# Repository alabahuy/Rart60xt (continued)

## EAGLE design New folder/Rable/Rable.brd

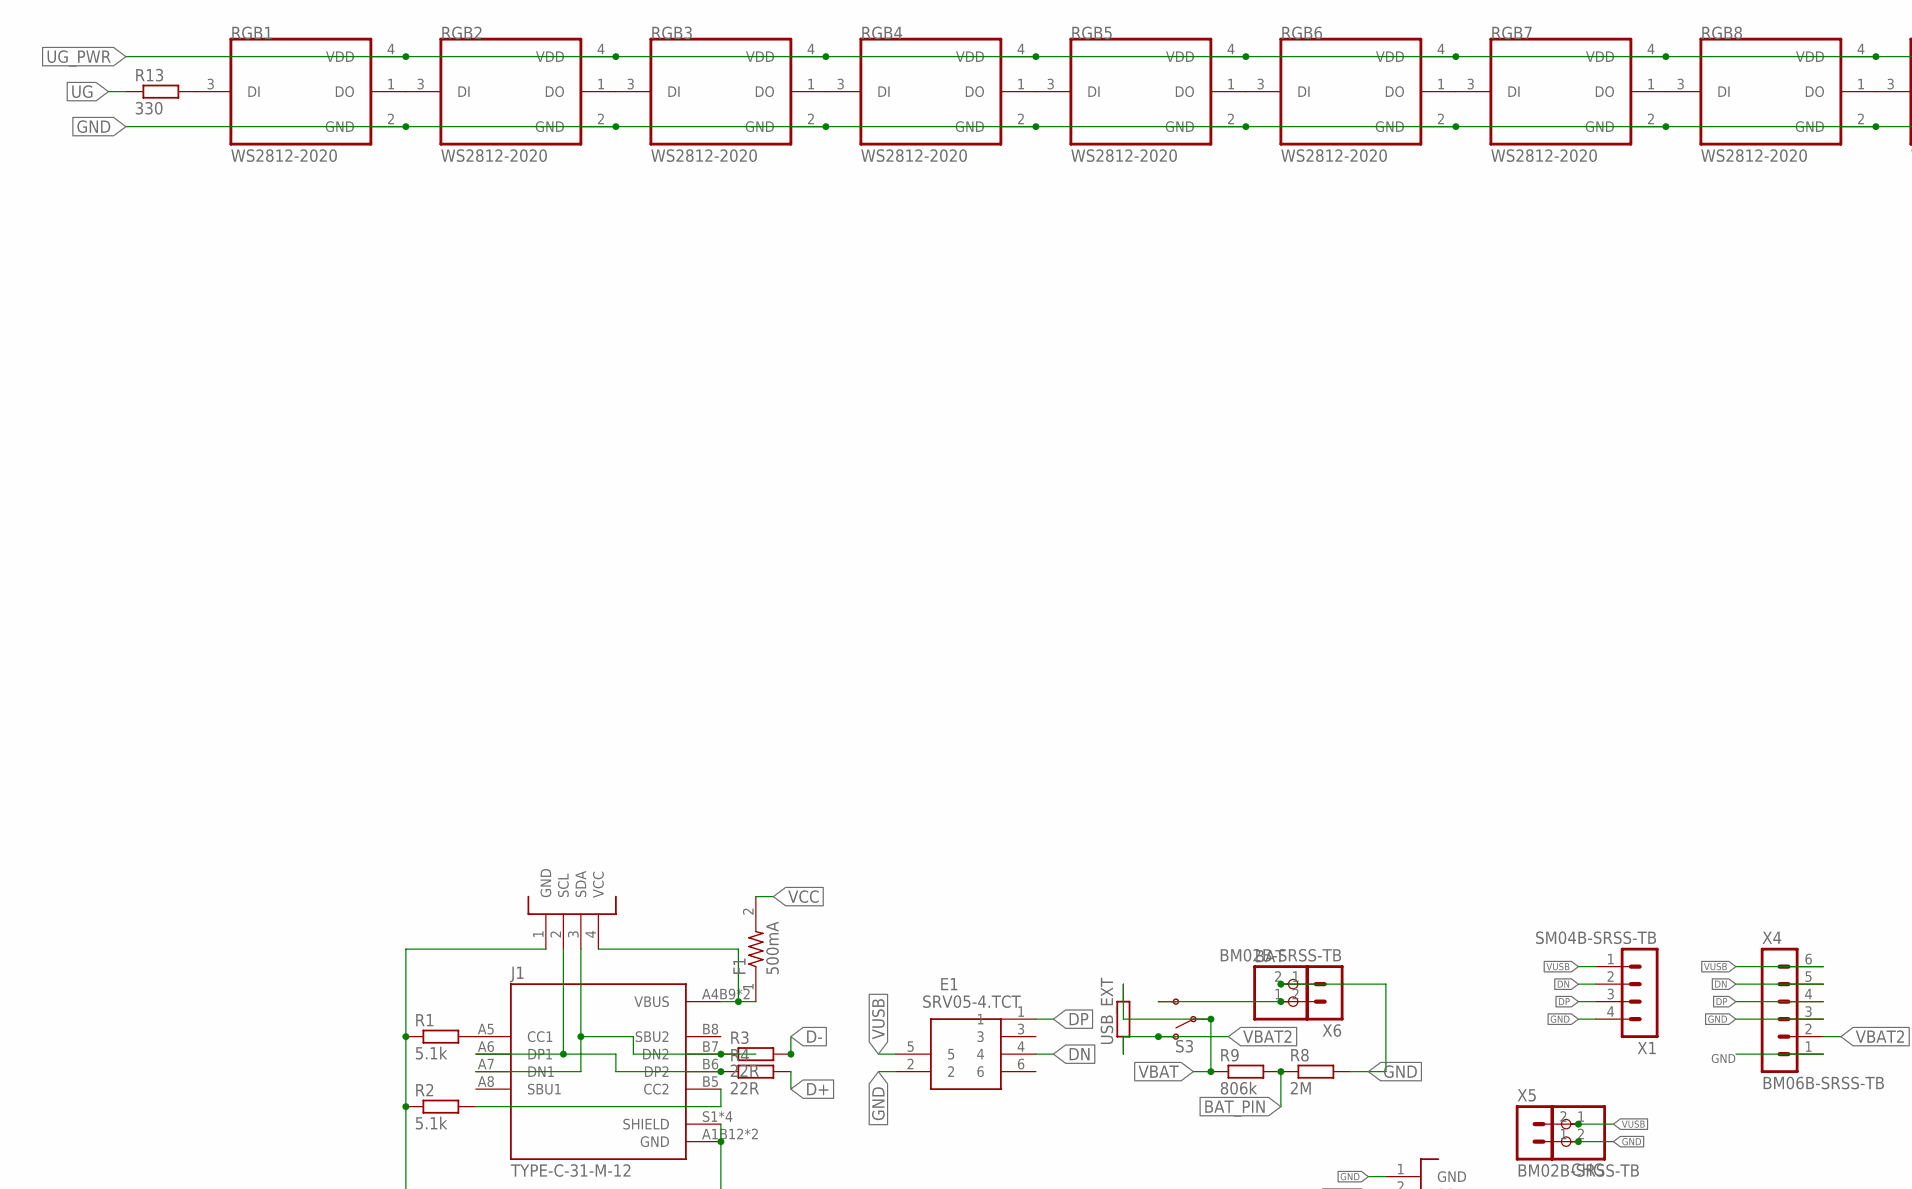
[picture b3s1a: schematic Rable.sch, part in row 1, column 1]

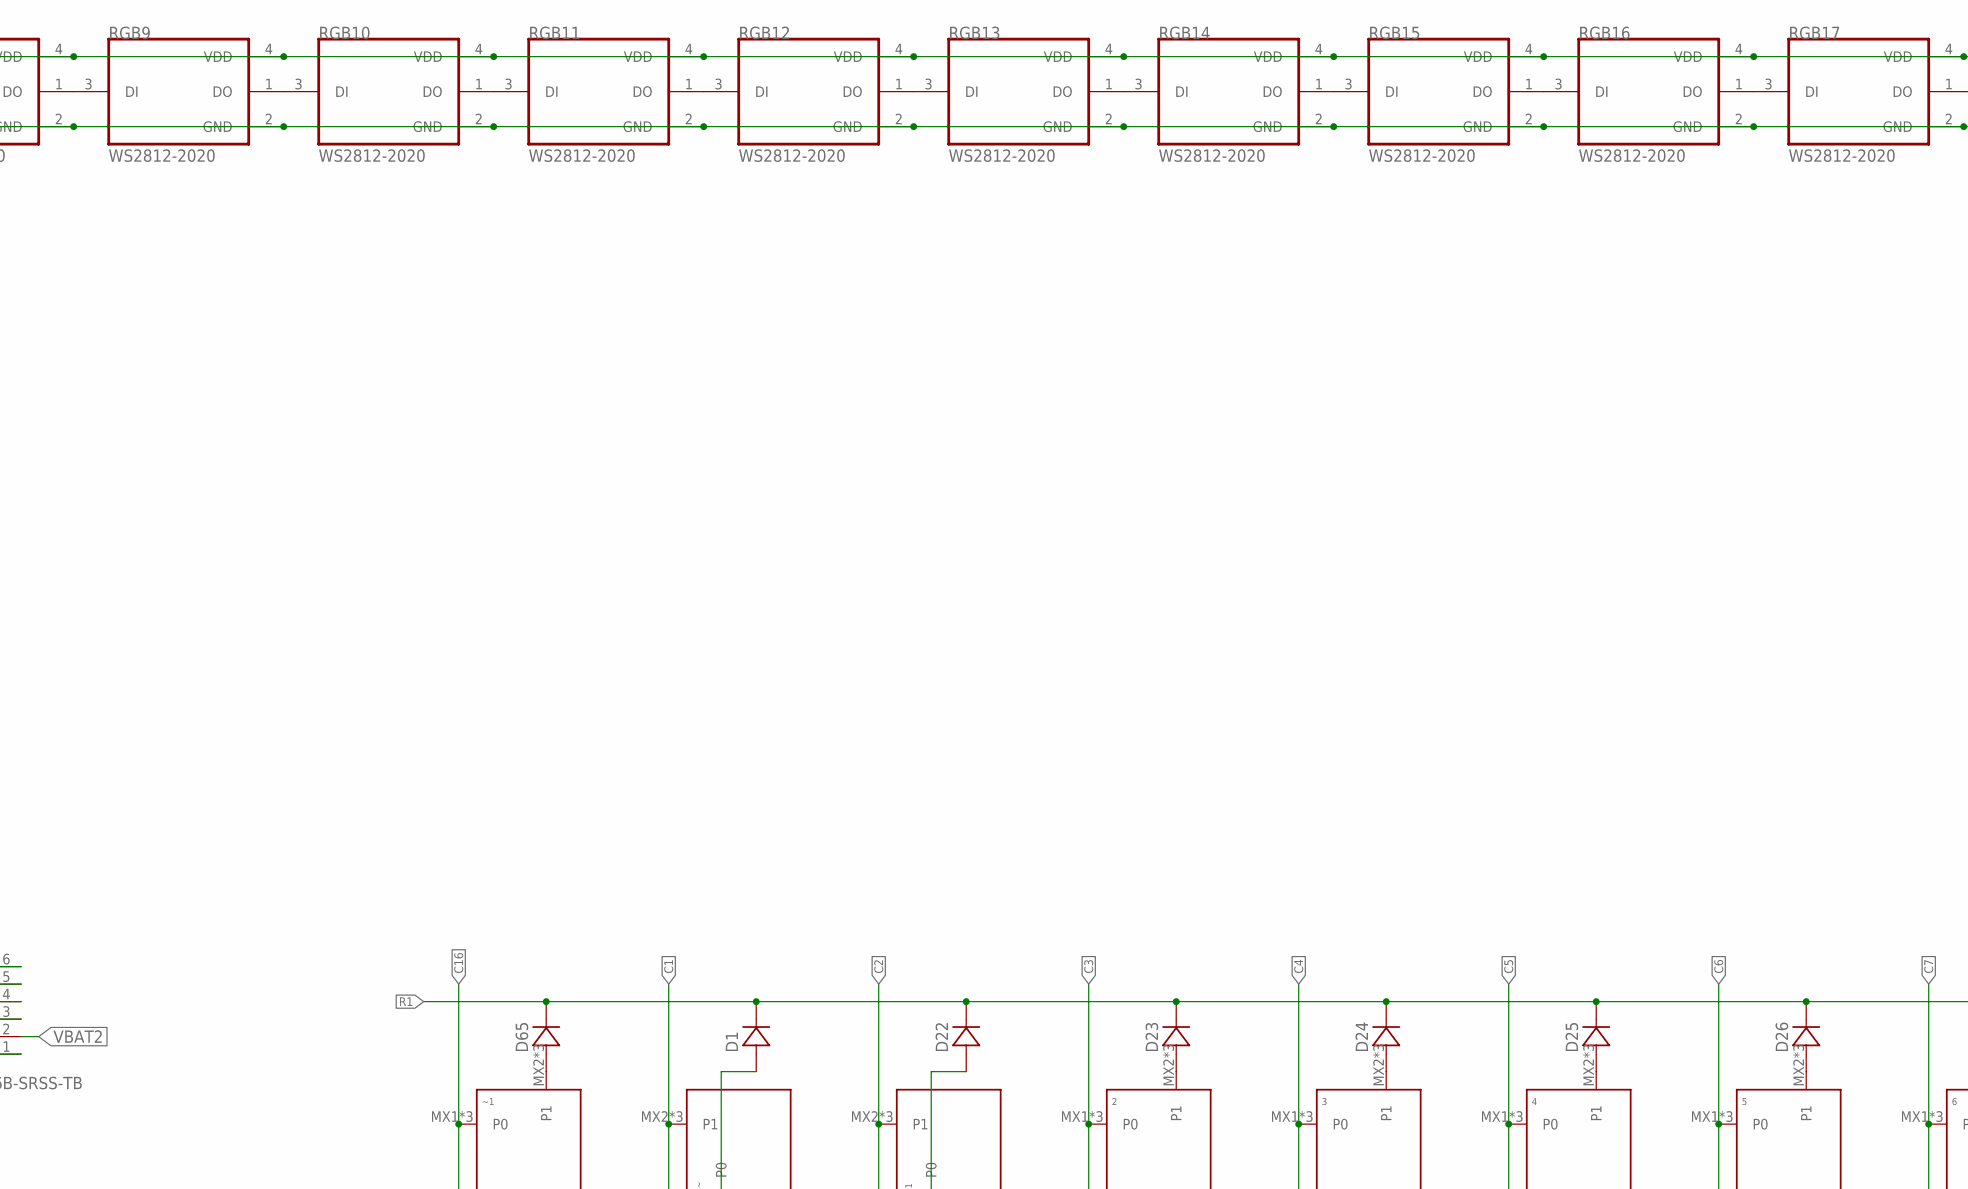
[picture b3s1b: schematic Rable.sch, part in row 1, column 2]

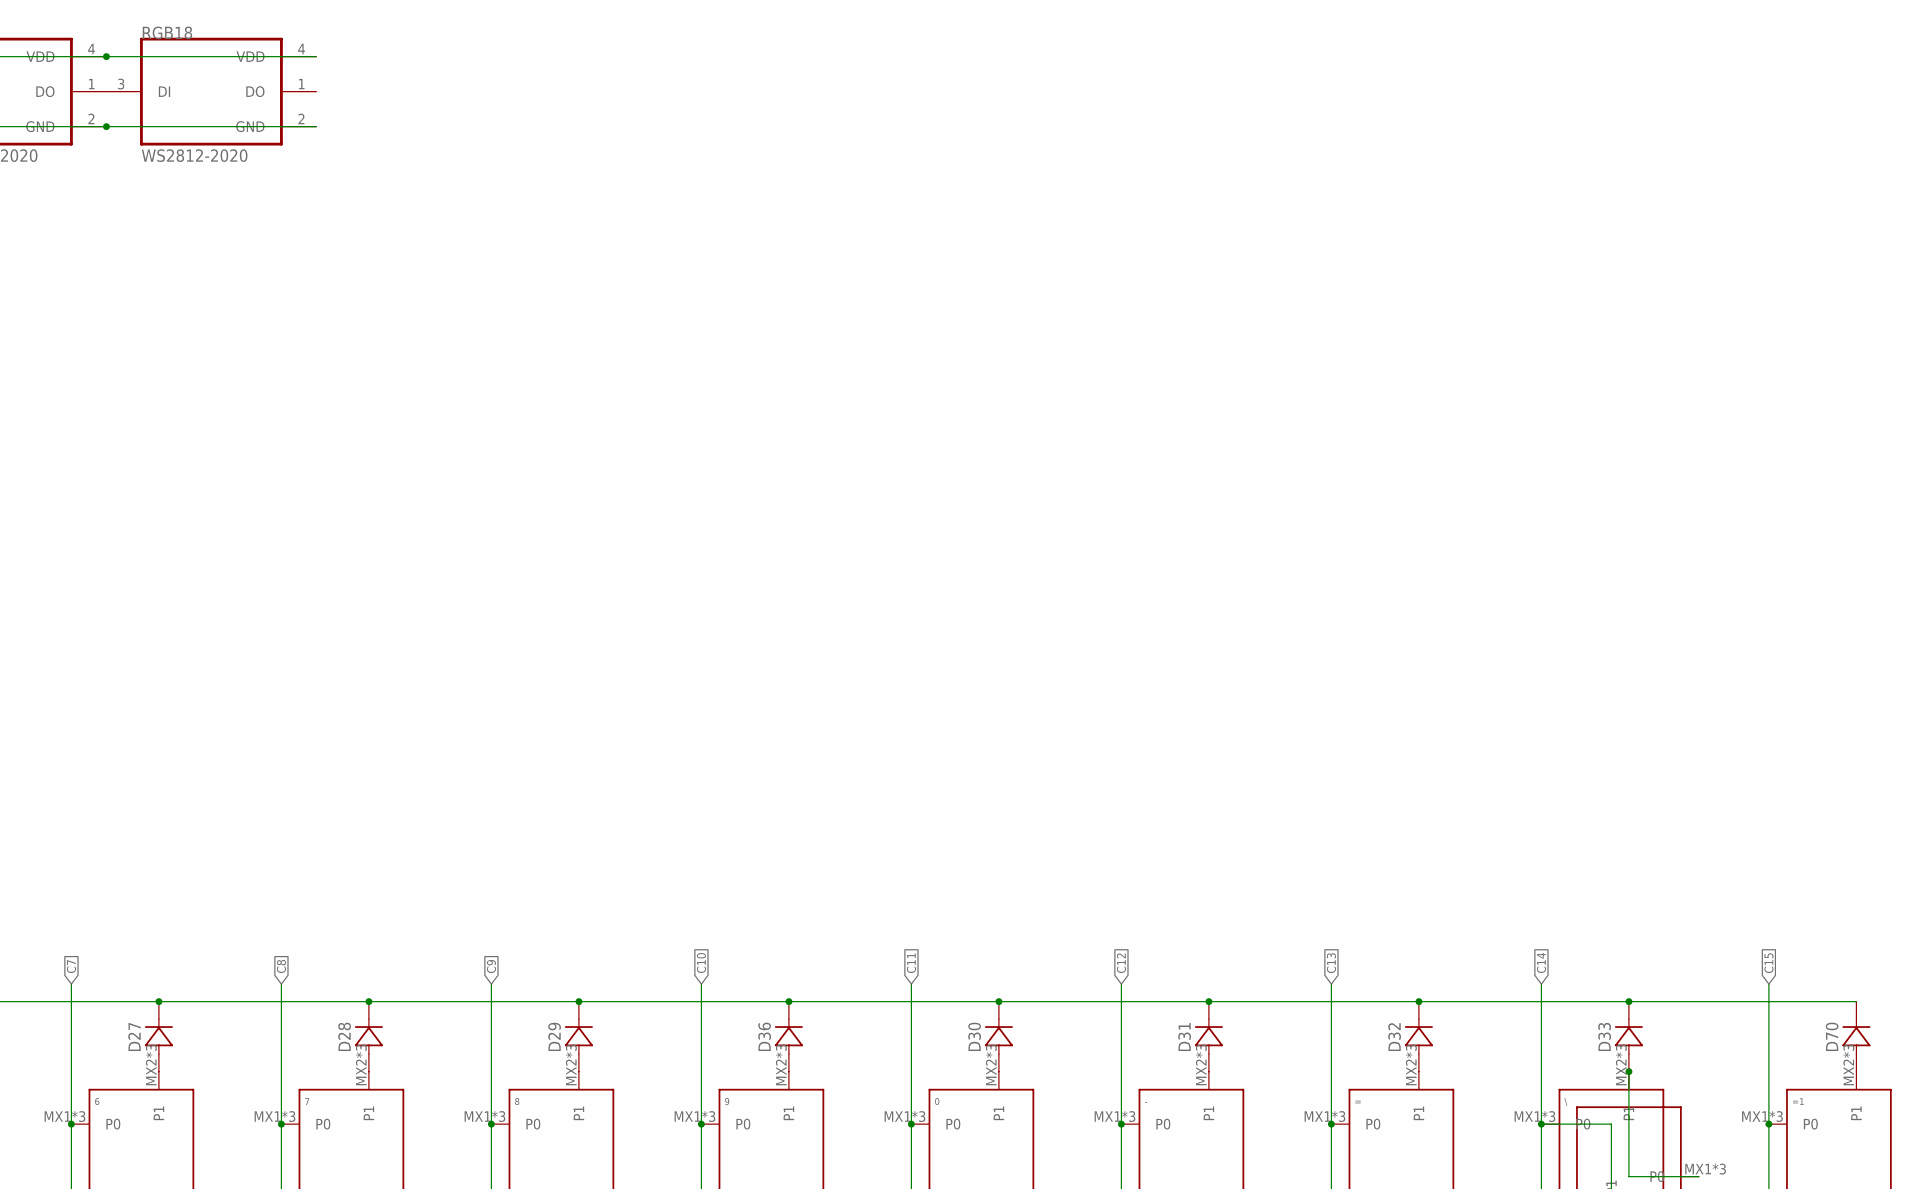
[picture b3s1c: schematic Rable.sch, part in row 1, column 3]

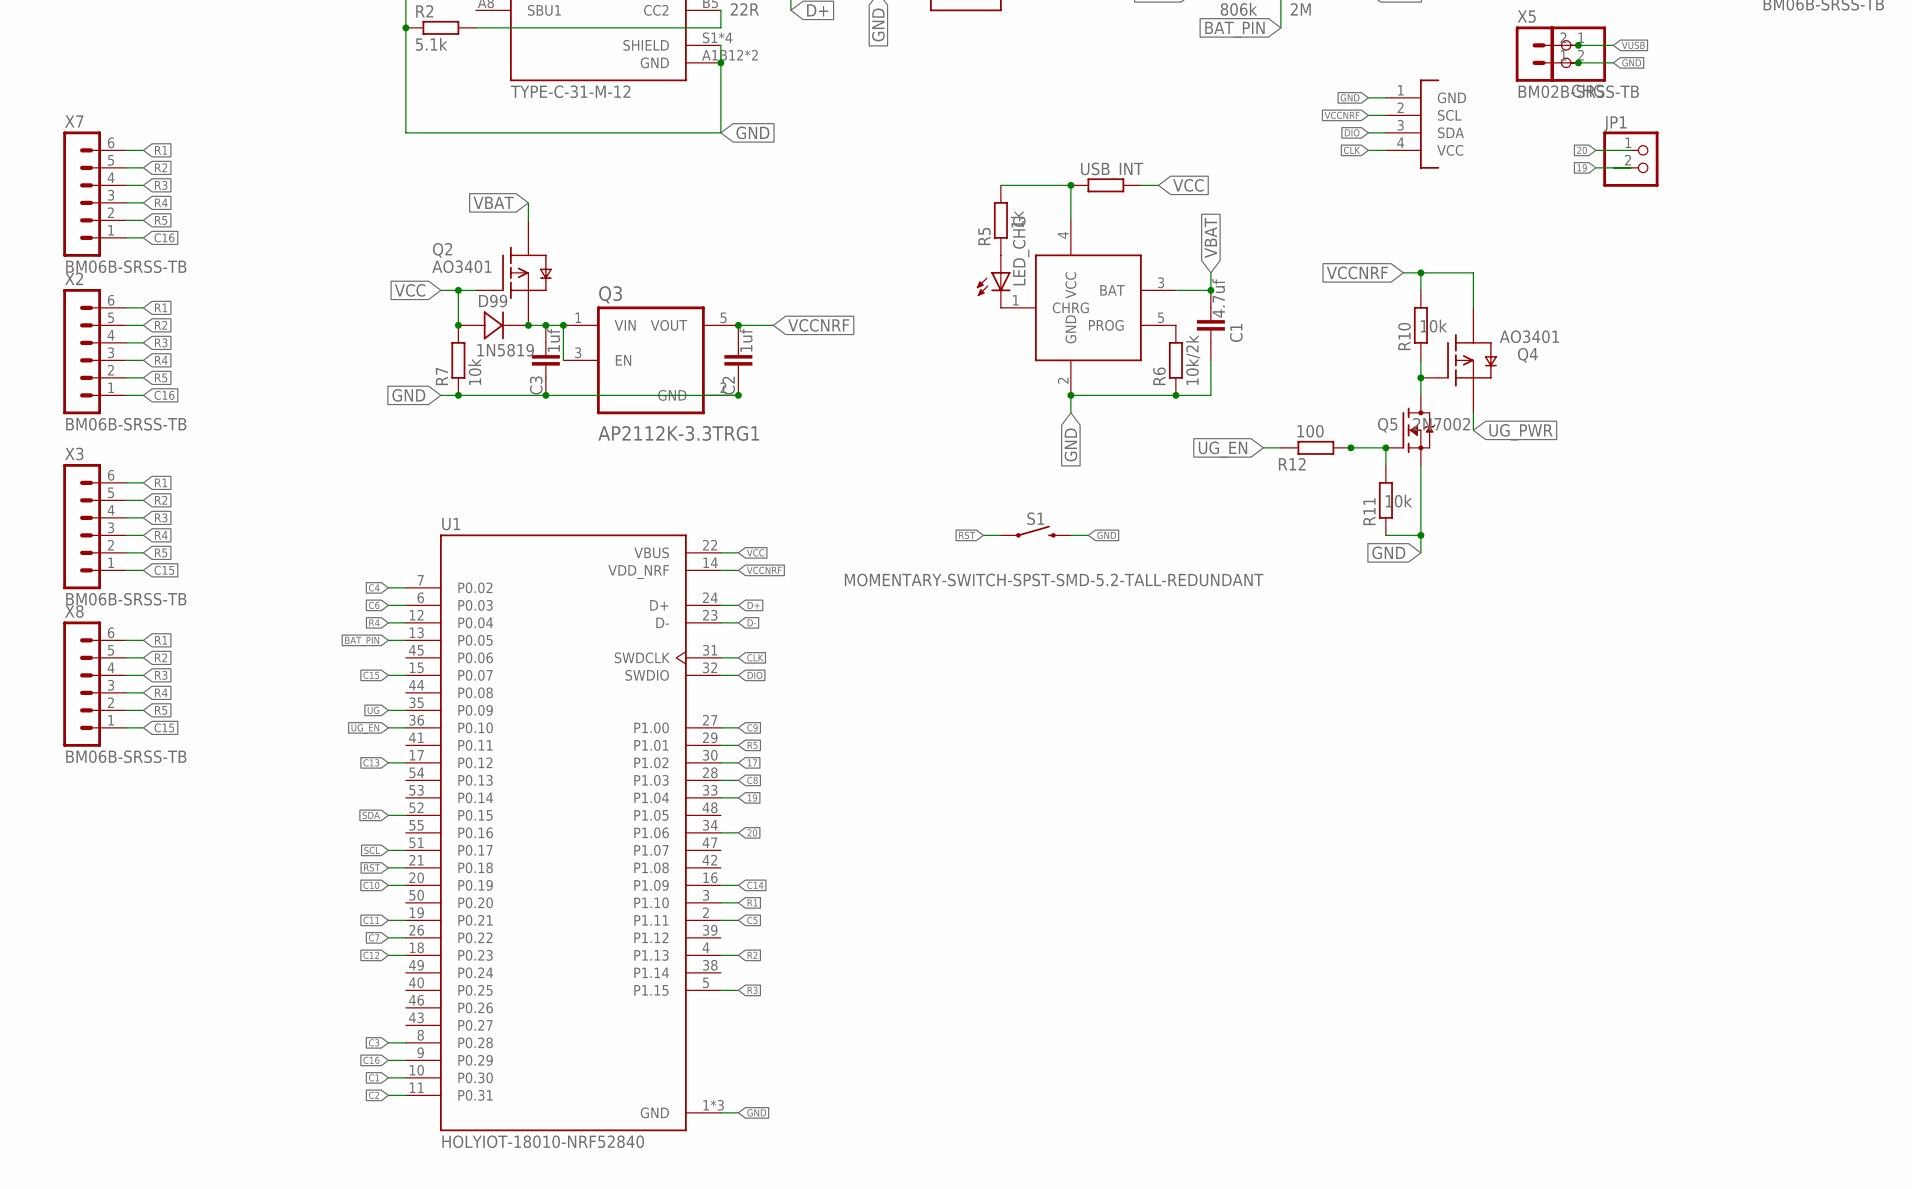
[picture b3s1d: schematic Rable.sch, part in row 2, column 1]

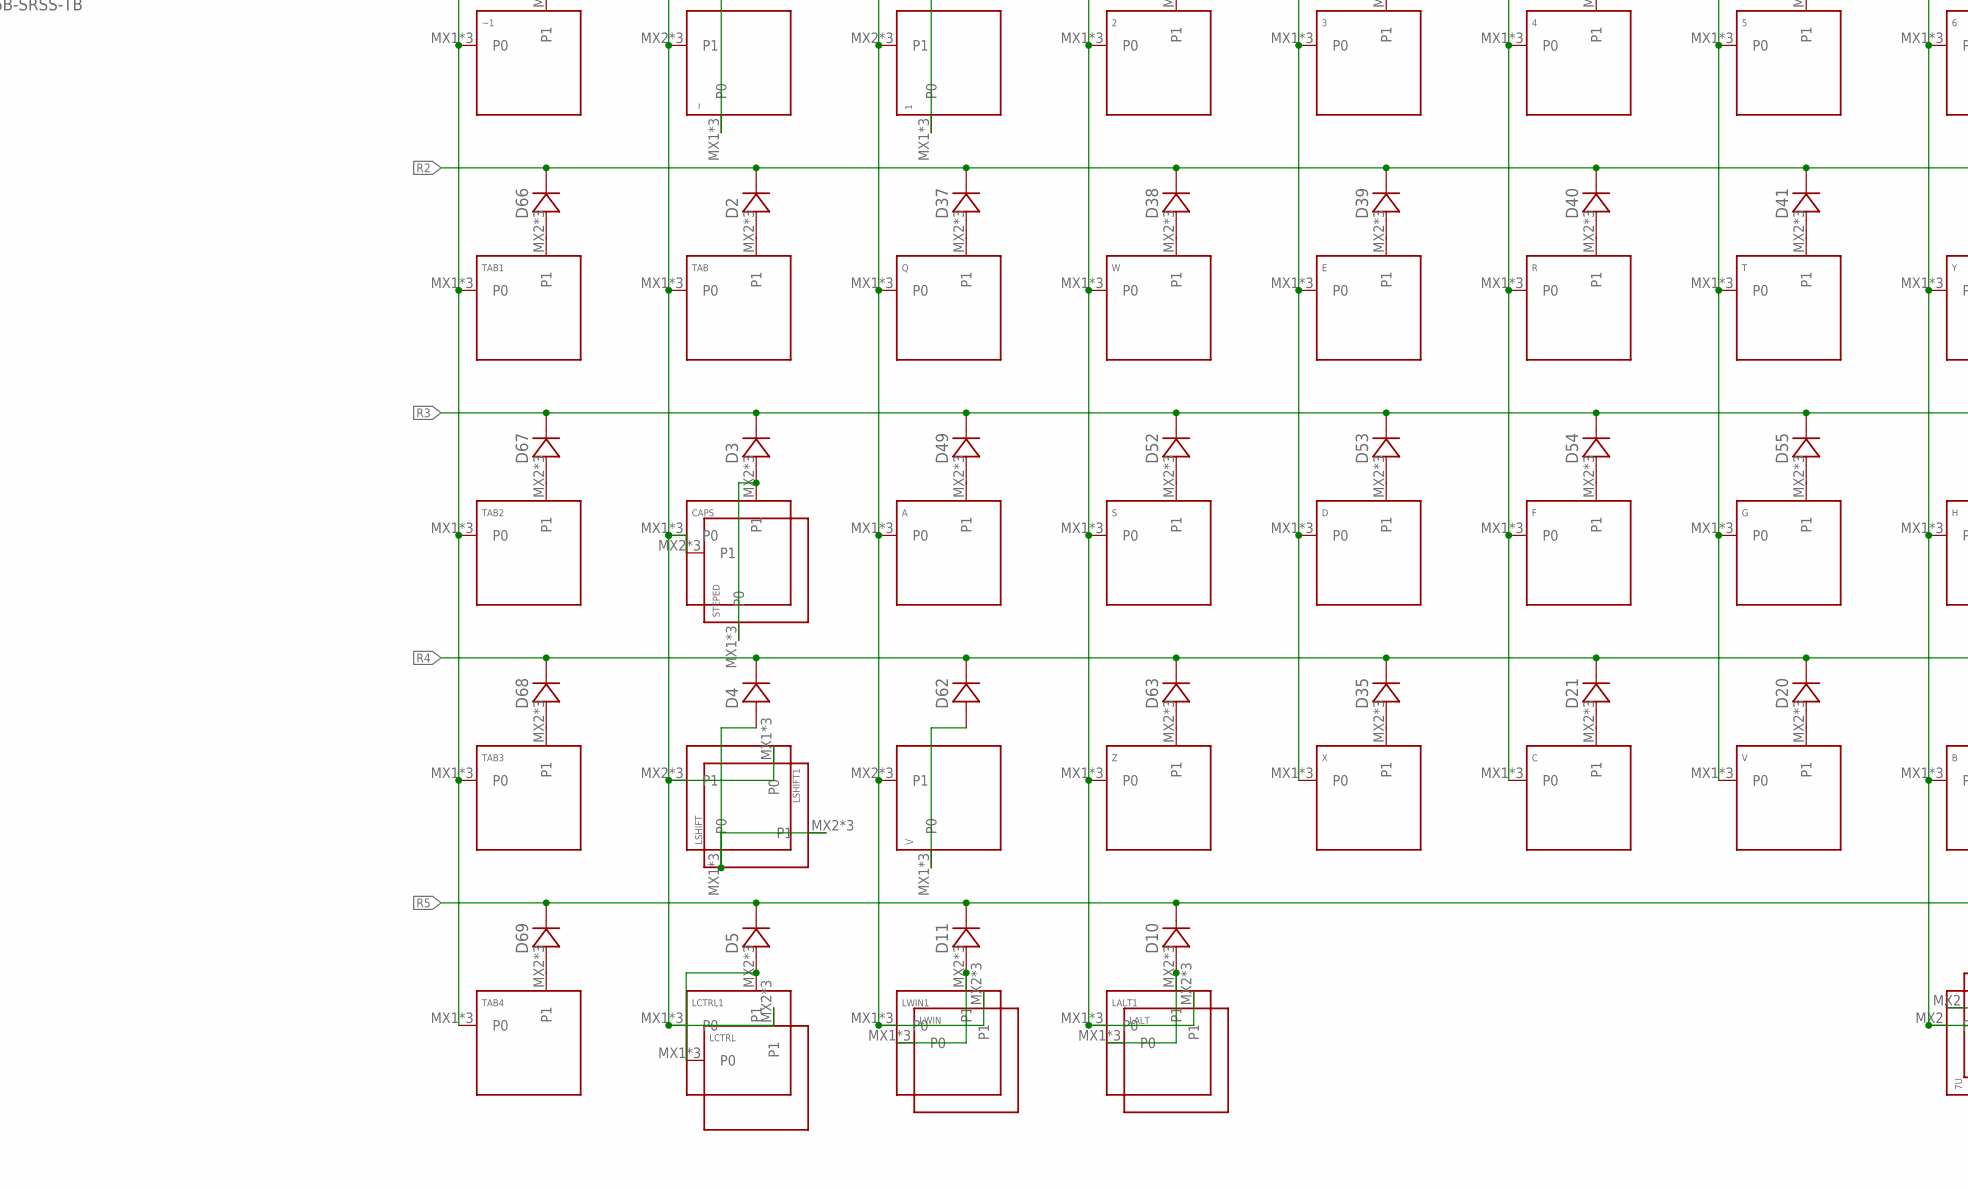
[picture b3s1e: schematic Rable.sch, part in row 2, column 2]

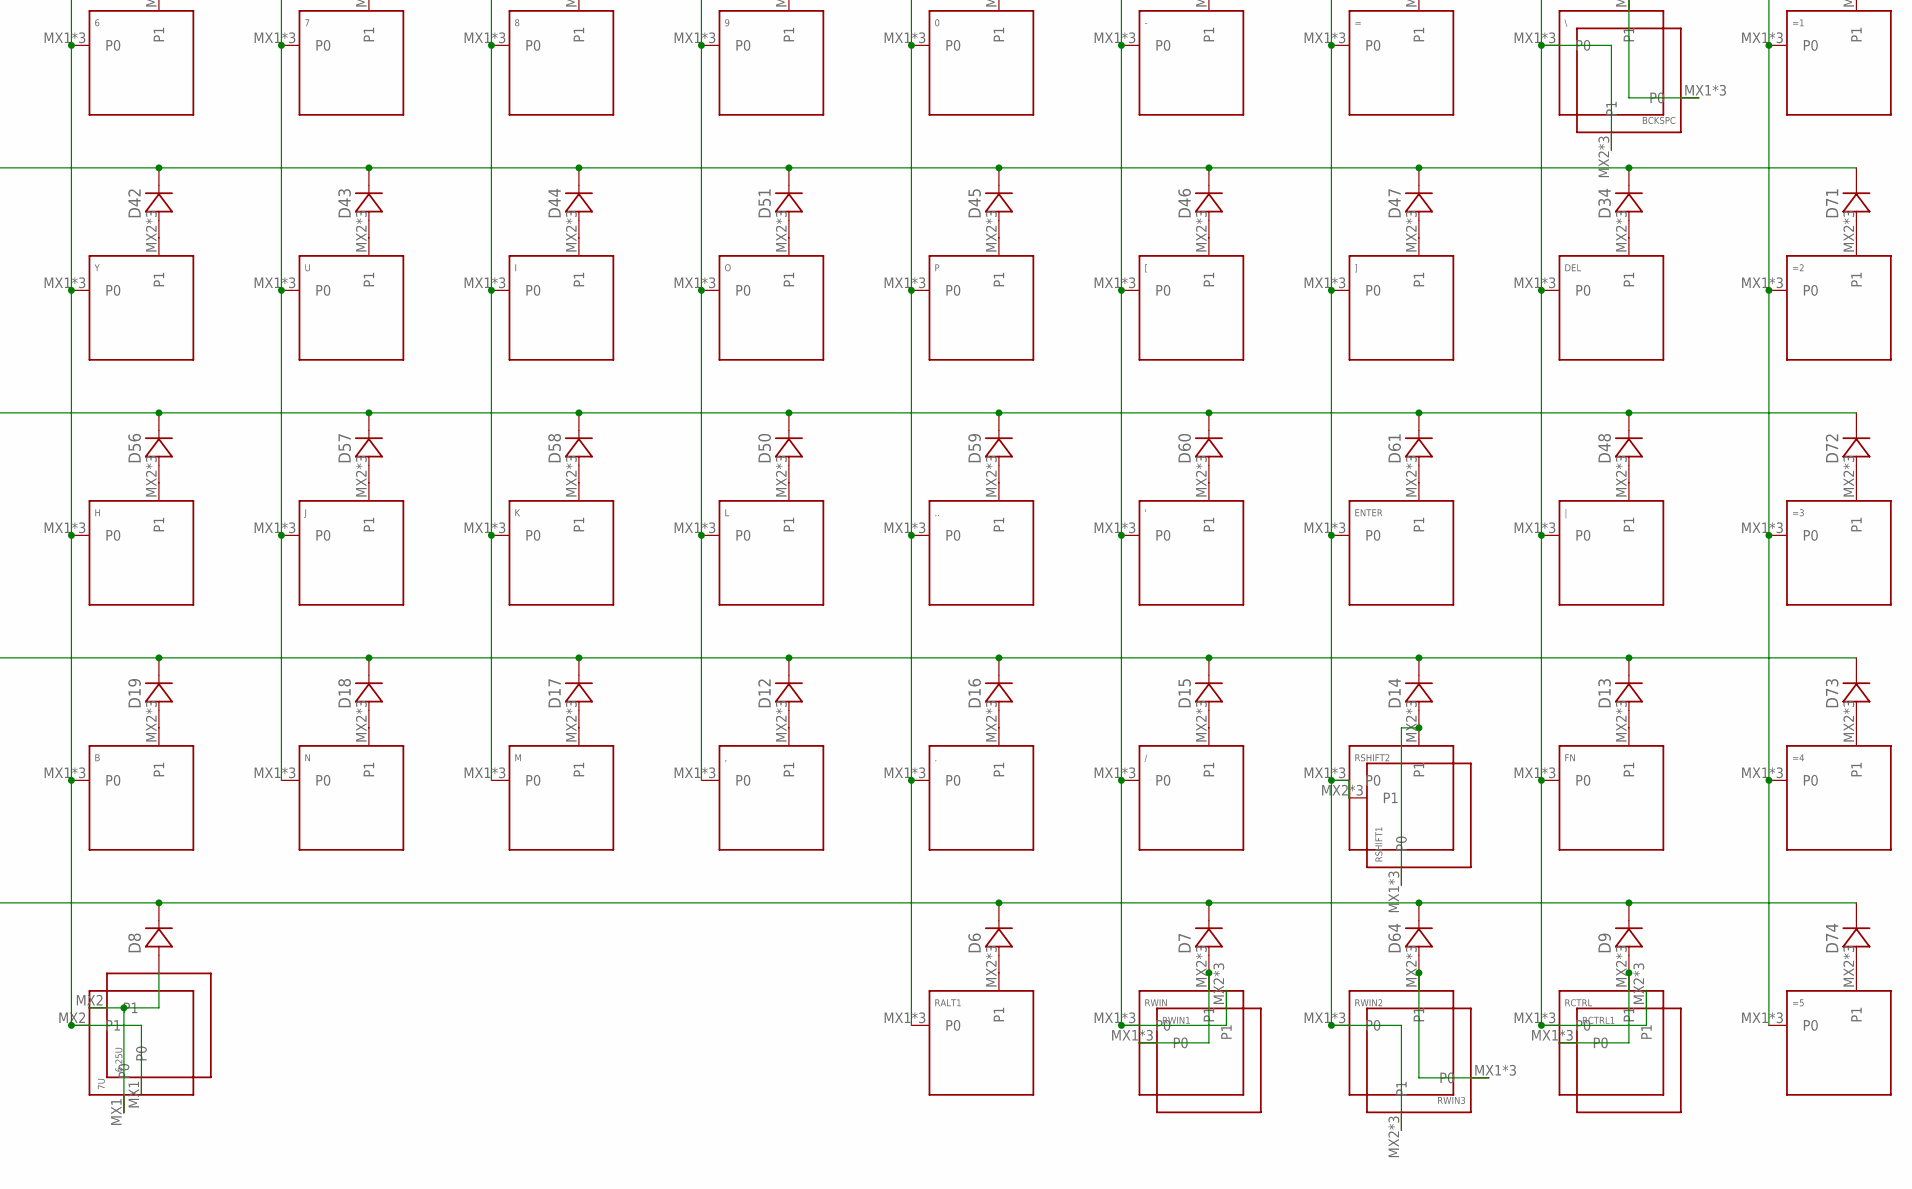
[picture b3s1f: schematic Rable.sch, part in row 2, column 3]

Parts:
0, 1, 2, 3, 4, 5, 6, 7, 8, 9, ., ..: KEYSWITCH-PLAIN-MXHSPCB-1U; MXHSPCB-1U
6.25U: KEYSWITCH-PLAIN-MXHSPCB-6.25U-FLIPPED; MXHSPCB-6.25U-FLIPPED
7U: KEYSWITCH-PLAIN-MXHSPCB-7U; MXHSPCB-7U
': KEYSWITCH-PLAIN-MXHSPCB-1U; MXHSPCB-1U
,: KEYSWITCH-PLAIN-MXHSPCB-1U; MXHSPCB-1U
-: KEYSWITCH-PLAIN-MXHSPCB-1U; MXHSPCB-1U
/: KEYSWITCH-PLAIN-MXHSPCB-1U; MXHSPCB-1U
=, =1, =2, =3, =4, =5: KEYSWITCH-PLAIN-MXHSPCB-1U; MXHSPCB-1U
A: KEYSWITCH-PLAIN-MXHSPCB-1U; MXHSPCB-1U
B: KEYSWITCH-PLAIN-MXHSPCB-1U; MXHSPCB-1U
BAT: JST_2PIN-THM-RA; JST-PH-2-THM-RA
BCKSPC: KEYSWITCH-PLAIN-MXHSPCB-2U; MXHSPCB-2U
C: KEYSWITCH-PLAIN-MXHSPCB-1U; MXHSPCB-1U
C1: 4.7uf; C0805
C2, C3: 1uf; C0805
CAPS: KEYSWITCH-PLAIN-MXHSPCB-1U; MXHSPCB-1U
CHG: JST_2PIN-THM-RA; JST-PH-2-THM-RA
D: KEYSWITCH-PLAIN-MXHSPCB-1U; MXHSPCB-1U
D1, D2, D3, D4, D5, D6, D7, D8, D9, D10, D11, D12, D13, D14, D15, D16, D17, D18, D19, D20, D21, D22, D23, D24, D25, D26, D27, D28, D29, D30, D31, D32, D33, D34, D35, D36, D37, D38, D39, D40, D41, D42, D43, D44, D45, D46, D47, D48, D49, D50, D51, D52, D53, D54, D55, D56, D57, D58, D59, D60, D61, D62, D63, D64, D65, D66, D67, D68, D69, D70, D71, D72, D73, D74: DIODE-SOD-123; SOD-123
D99: 1N5819; SOD-123
DEL: KEYSWITCH-PLAIN-MXHSPCB-1U; MXHSPCB-1U
E: KEYSWITCH-PLAIN-MXHSPCB-1U; MXHSPCB-1U
E1: SRV05-4.TCT; SOT95P280X145-6N
ENTER: KEYSWITCH-PLAIN-MXHSPCB-2U-FLIPPED; MXHSPCB-2U-FLIPPED
F: KEYSWITCH-PLAIN-MXHSPCB-1U; MXHSPCB-1U
F1: 500mA; RESC3216X125N
FN: KEYSWITCH-PLAIN-MXHSPCB-1U; MXHSPCB-1U
G: KEYSWITCH-PLAIN-MXHSPCB-1U; MXHSPCB-1U
H: KEYSWITCH-PLAIN-MXHSPCB-1U; MXHSPCB-1U
I: KEYSWITCH-PLAIN-MXHSPCB-1U; MXHSPCB-1U
J: KEYSWITCH-PLAIN-MXHSPCB-1U; MXHSPCB-1U
J1: TYPE-C-31-M-12; HRO_TYPE-C-31-M-12
J3, J4: I2C-HEADER; HEADER-4X1-2.54
JP1: PINHD-1X2M; 1X02M
K: KEYSWITCH-PLAIN-MXHSPCB-1U; MXHSPCB-1U
L: KEYSWITCH-PLAIN-MXHSPCB-1U; MXHSPCB-1U
LALT, LALT1: KEYSWITCH-PLAIN-MXHSPCB-1U; MXHSPCB-1U
LCTRL, LCTRL1: KEYSWITCH-PLAIN-MXHSPCB-1U; MXHSPCB-1U
LED_CHG: LEDCHIPLED_1206; CHIPLED_1206
LSHIFT: KEYSWITCH-PLAIN-MXHSPCB-1U; MXHSPCB-1U
LSHIFT1: KEYSWITCH-PLAIN-MXHSPCB-2U; MXHSPCB-2U
LWIN, LWIN1: KEYSWITCH-PLAIN-MXHSPCB-1U; MXHSPCB-1U
M: KEYSWITCH-PLAIN-MXHSPCB-1U; MXHSPCB-1U
N: KEYSWITCH-PLAIN-MXHSPCB-1U; MXHSPCB-1U
O: KEYSWITCH-PLAIN-MXHSPCB-1U; MXHSPCB-1U
P: KEYSWITCH-PLAIN-MXHSPCB-1U; MXHSPCB-1U
Q: KEYSWITCH-PLAIN-MXHSPCB-1U; MXHSPCB-1U
Q1: LTC4054
Q2, Q4: AO3401; SOT23-3
Q3: AP2112K-3.3TRG1; SOT95P285X140-5N
Q5: 2N7002; SOT95P240X111-3N
R: KEYSWITCH-PLAIN-MXHSPCB-1U; MXHSPCB-1U
R1, R2: 5.1k; R0805
R3, R4: 22R; R0805
R5: 1k; R0805
R6: 10k/2k; R0805
R7, R10, R11: 10k; R0805
R8: 2M; R0805
R9: 806k; R0805
R12: 100; R0805
R13: 330; R0805
RALT1: KEYSWITCH-PLAIN-MXHSPCB-1U; MXHSPCB-1U
RCTRL, RCTRL1: KEYSWITCH-PLAIN-MXHSPCB-1U; MXHSPCB-1U
RGB1, RGB2, RGB3, RGB4, RGB5, RGB6, RGB7, RGB8, RGB9, RGB10, RGB11, RGB12, RGB13, RGB14, RGB15, RGB16, RGB17, RGB18: WS2812-2020; LED_WS2812-2020
RSHIFT1: KEYSWITCH-PLAIN-MXHSPCB-2U-FLIPPED; MXHSPCB-2U-FLIPPED
RSHIFT2: KEYSWITCH-PLAIN-MXHSPCB-1U; MXHSPCB-1U
RWIN, RWIN1, RWIN2, RWIN3: KEYSWITCH-PLAIN-MXHSPCB-1U; MXHSPCB-1U
S: KEYSWITCH-PLAIN-MXHSPCB-1U; MXHSPCB-1U
S1: MOMENTARY-SWITCH-SPST-SMD-5.2-TALL-REDUNDANT; TACTILE_SWITCH_SMD_5.2MM
S3: SWITCH-SPDT-SMD-AYZ0202; SWITCH_DPDT_SMD_AYZ0202
STEPED: KEYSWITCH-PLAIN-MXHSPCB-1U; MXHSPCB-1U
T: KEYSWITCH-PLAIN-MXHSPCB-1U; MXHSPCB-1U
TAB, TAB1, TAB2, TAB3, TAB4: KEYSWITCH-PLAIN-MXHSPCB-1U; MXHSPCB-1U
U: KEYSWITCH-PLAIN-MXHSPCB-1U; MXHSPCB-1U
U1: HOLYIOT-18010-NRF52840; XCVR_HOLYIOT-18010-NRF52840
USB_EXT: RESISTOR-0405; R0402
USB_INT: RESISTOR-0405; R0402
V: KEYSWITCH-PLAIN-MXHSPCB-1U; MXHSPCB-1U
W: KEYSWITCH-PLAIN-MXHSPCB-1U; MXHSPCB-1U
X: KEYSWITCH-PLAIN-MXHSPCB-1U; MXHSPCB-1U
X1: SM04B-SRSS-TB
X2, X3, X4, X7, X8: BM06B-SRSS-TB
X5, X6: BM02B-SRSS-TB
Y: KEYSWITCH-PLAIN-MXHSPCB-1U; MXHSPCB-1U
Z: KEYSWITCH-PLAIN-MXHSPCB-1U; MXHSPCB-1U
[: KEYSWITCH-PLAIN-MXHSPCB-1U; MXHSPCB-1U
\/: KEYSWITCH-PLAIN-MXHSPCB-1U; MXHSPCB-1U
\\: KEYSWITCH-PLAIN-MXHSPCB-1U; MXHSPCB-1U
]: KEYSWITCH-PLAIN-MXHSPCB-1U; MXHSPCB-1U
|: KEYSWITCH-PLAIN-MXHSPCB-1U; MXHSPCB-1U
~, ~1: KEYSWITCH-PLAIN-MXHSPCB-1U; MXHSPCB-1U

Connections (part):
17: U1.30 (P1.02)
19: JP1.2, U1.33 (P1.04)
20: JP1.1, U1.34 (P1.06)
BAT_PIN: R8.1, R9.2, U1.13 (P0.05)
C1: CAPS.MX1 (P0), CAPS.P$1 (P0), CAPS.P$2 (P0), LCTRL.MX2 (P1), LCTRL.P$3 (P1), LCTRL.P$4 (P1), LCTRL1.MX1 (P0), LCTRL1.P$1 (P0), LCTRL1.P$2 (P0), LSHIFT.MX2 (P1), LSHIFT.P$3 (P1), LSHIFT.P$4 (P1), LSHIFT1.MX1 (P0), LSHIFT1.P$1 (P0), LSHIFT1.P$2 (P0), STEPED.MX2 (P1), STEPED.P$3 (P1), STEPED.P$4 (P1), TAB.MX1 (P0), TAB.P$1 (P0), TAB.P$2 (P0), U1.10 (P0.30), ~.MX2 (P1), ~.P$3 (P1), ~.P$4 (P1)
C2: 1.MX2 (P1), 1.P$3 (P1), 1.P$4 (P1), A.MX1 (P0), A.P$1 (P0), A.P$2 (P0), LWIN.MX2 (P1), LWIN.P$3 (P1), LWIN.P$4 (P1), LWIN1.MX1 (P0), LWIN1.P$1 (P0), LWIN1.P$2 (P0), Q.MX1 (P0), Q.P$1 (P0), Q.P$2 (P0), U1.11 (P0.31), \/.MX2 (P1), \/.P$3 (P1), \/.P$4 (P1)
C3: 2.MX1 (P0), 2.P$1 (P0), 2.P$2 (P0), LALT.MX2 (P1), LALT.P$3 (P1), LALT.P$4 (P1), LALT1.MX1 (P0), LALT1.P$1 (P0), LALT1.P$2 (P0), S.MX1 (P0), S.P$1 (P0), S.P$2 (P0), U1.8 (P0.28), W.MX1 (P0), W.P$1 (P0), W.P$2 (P0), Z.MX1 (P0), Z.P$1 (P0), Z.P$2 (P0)
C4: 3.MX1 (P0), 3.P$1 (P0), 3.P$2 (P0), D.MX1 (P0), D.P$1 (P0), D.P$2 (P0), E.MX1 (P0), E.P$1 (P0), E.P$2 (P0), U1.7 (P0.02), X.MX1 (P0), X.P$1 (P0), X.P$2 (P0)
C5: 4.MX1 (P0), 4.P$1 (P0), 4.P$2 (P0), C.MX1 (P0), C.P$1 (P0), C.P$2 (P0), F.MX1 (P0), F.P$1 (P0), F.P$2 (P0), R.MX1 (P0), R.P$1 (P0), R.P$2 (P0), U1.2 (P1.11)
C6: 5.MX1 (P0), 5.P$1 (P0), 5.P$2 (P0), G.MX1 (P0), G.P$1 (P0), G.P$2 (P0), T.MX1 (P0), T.P$1 (P0), T.P$2 (P0), U1.6 (P0.03), V.MX1 (P0), V.P$1 (P0), V.P$2 (P0)
C7: 6.MX1 (P0), 6.P$1 (P0), 6.P$2 (P0), 6.25U.MX1 (P0), 7U.MX2 (P1), B.MX1 (P0), B.P$1 (P0), B.P$2 (P0), H.MX1 (P0), H.P$1 (P0), H.P$2 (P0), U1.26 (P0.22), Y.MX1 (P0), Y.P$1 (P0), Y.P$2 (P0)
C8: 7.MX1 (P0), 7.P$1 (P0), 7.P$2 (P0), J.MX1 (P0), J.P$1 (P0), J.P$2 (P0), N.MX1 (P0), N.P$1 (P0), N.P$2 (P0), U.MX1 (P0), U.P$1 (P0), U.P$2 (P0), U1.28 (P1.03)
C9: 8.MX1 (P0), 8.P$1 (P0), 8.P$2 (P0), I.MX1 (P0), I.P$1 (P0), I.P$2 (P0), K.MX1 (P0), K.P$1 (P0), K.P$2 (P0), M.MX1 (P0), M.P$1 (P0), M.P$2 (P0), U1.27 (P1.00)
C10: 9.MX1 (P0), 9.P$1 (P0), 9.P$2 (P0), ,.MX1 (P0), ,.P$1 (P0), ,.P$2 (P0), L.MX1 (P0), L.P$1 (P0), L.P$2 (P0), O.MX1 (P0), O.P$1 (P0), O.P$2 (P0), U1.20 (P0.19)
C11: 0.MX1 (P0), 0.P$1 (P0), 0.P$2 (P0), ..MX1 (P0), ..P$1 (P0), ..P$2 (P0), ...MX1 (P0), ...P$1 (P0), ...P$2 (P0), P.MX1 (P0), P.P$1 (P0), P.P$2 (P0), RALT1.MX1 (P0), RALT1.P$1 (P0), RALT1.P$2 (P0), U1.19 (P0.21)
C12: '.MX1 (P0), '.P$1 (P0), '.P$2 (P0), -.MX1 (P0), -.P$1 (P0), -.P$2 (P0), /.MX1 (P0), /.P$1 (P0), /.P$2 (P0), RWIN.MX1 (P0), RWIN.P$1 (P0), RWIN.P$2 (P0), RWIN1.MX2 (P1), RWIN1.P$3 (P1), RWIN1.P$4 (P1), U1.18 (P0.23), [.MX1 (P0), [.P$1 (P0), [.P$2 (P0)
C13: =.MX1 (P0), =.P$1 (P0), =.P$2 (P0), ENTER.MX1 (P0), ENTER.P$1 (P0), ENTER.P$2 (P0), RSHIFT1.MX2 (P1), RSHIFT1.P$3 (P1), RSHIFT1.P$4 (P1), RSHIFT2.MX1 (P0), RSHIFT2.P$1 (P0), RSHIFT2.P$2 (P0), RWIN2.MX1 (P0), RWIN2.P$1 (P0), RWIN2.P$2 (P0), RWIN3.MX2 (P1), RWIN3.P$3 (P1), RWIN3.P$4 (P1), U1.17 (P0.12), ].MX1 (P0), ].P$1 (P0), ].P$2 (P0)
C14: BCKSPC.MX2 (P1), BCKSPC.P$3 (P1), BCKSPC.P$4 (P1), DEL.MX1 (P0), DEL.P$1 (P0), DEL.P$2 (P0), FN.MX1 (P0), FN.P$1 (P0), FN.P$2 (P0), RCTRL.MX1 (P0), RCTRL.P$1 (P0), RCTRL.P$2 (P0), RCTRL1.MX2 (P1), RCTRL1.P$3 (P1), RCTRL1.P$4 (P1), U1.16 (P1.09), \\.MX1 (P0), \\.P$1 (P0), \\.P$2 (P0), |.MX1 (P0), |.P$1 (P0), |.P$2 (P0)
C15: =1.MX1 (P0), =1.P$1 (P0), =1.P$2 (P0), =2.MX1 (P0), =2.P$1 (P0), =2.P$2 (P0), =3.MX1 (P0), =3.P$1 (P0), =3.P$2 (P0), =4.MX1 (P0), =4.P$1 (P0), =4.P$2 (P0), =5.MX1 (P0), =5.P$1 (P0), =5.P$2 (P0), U1.15 (P0.07), X3.1, X8.1
C16: TAB1.MX1 (P0), TAB1.P$1 (P0), TAB1.P$2 (P0), TAB2.MX1 (P0), TAB2.P$1 (P0), TAB2.P$2 (P0), TAB3.MX1 (P0), TAB3.P$1 (P0), TAB3.P$2 (P0), TAB4.MX1 (P0), TAB4.P$1 (P0), TAB4.P$2 (P0), U1.9 (P0.29), X2.1, X7.1, ~1.MX1 (P0), ~1.P$1 (P0), ~1.P$2 (P0)
CLK: J3.4 (VCC), U1.31 (SWDCLK)
D+: R4.2, U1.24 (D+)
D-: R3.2, U1.23 (D-)
DIO: J3.3 (SDA), U1.32 (SWDIO)
DN: E1.4, J1.A7 (DN1), J1.B7 (DN2), J4.3 (SDA), R3.1, X1.2, X4.5
DP: E1.1, J1.A6 (DP1), J1.B6 (DP2), J4.2 (SCL), R4.1, X1.3, X4.4
GND: BAT.2 (1), C1.1, C2.1, C3.1, CHG.2 (1), E1.2, J1.A1B12 (GND), J1.B1A12 (GND), J1.S1 (SHIELD), J1.S2 (SHIELD), J1.S3 (SHIELD), J1.S4 (SHIELD), J3.1 (GND), J4.1 (GND), Q1.2 (GND), Q3.2 (GND), Q5.2 (S), R1.1, R2.1, R6.1, R7.1, R8.2, R11.1, RGB1.2 (GND), RGB2.2 (GND), RGB3.2 (GND), RGB4.2 (GND), RGB5.2 (GND), RGB6.2 (GND), RGB7.2 (GND), RGB8.2 (GND), RGB9.2 (GND), RGB10.2 (GND), RGB11.2 (GND), RGB12.2 (GND), RGB13.2 (GND), RGB14.2 (GND), RGB15.2 (GND), RGB16.2 (GND), RGB17.2 (GND), RGB18.2 (GND), S1.3 (2), S1.4 (2), U1.1 (GND), U1.25 (GND), U1.37 (GND), X1.4, X4.1, X4.3, X5.1, X6.1
unnamed: 6.25U.MX2 (P1), 7U.MX1 (P0), D8.A
unnamed: D1.A, ~.MX1 (P0), ~.P$1 (P0), ~.P$2 (P0)
unnamed: D2.A, TAB.MX2 (P1), TAB.P$3 (P1), TAB.P$4 (P1)
unnamed: CAPS.MX2 (P1), CAPS.P$3 (P1), CAPS.P$4 (P1), D3.A, STEPED.MX1 (P0), STEPED.P$1 (P0), STEPED.P$2 (P0)
unnamed: D62.A, \/.MX1 (P0), \/.P$1 (P0), \/.P$2 (P0)
unnamed: D5.A, LCTRL.MX1 (P0), LCTRL.P$1 (P0), LCTRL.P$2 (P0), LCTRL1.MX2 (P1), LCTRL1.P$3 (P1), LCTRL1.P$4 (P1)
unnamed: LED_CHG.C, Q1.1 (CHRG)
unnamed: D14.A, RSHIFT1.MX1 (P0), RSHIFT1.P$1 (P0), RSHIFT1.P$2 (P0), RSHIFT2.MX2 (P1), RSHIFT2.P$3 (P1), RSHIFT2.P$4 (P1)
unnamed: LED_CHG.A, R5.1
unnamed: C3.2, D99.C, Q2.2 (S), Q3.1 (VIN), Q3.3 (EN)
unnamed: D64.A, RWIN2.MX2 (P1), RWIN2.P$3 (P1), RWIN2.P$4 (P1), RWIN3.MX1 (P0), RWIN3.P$1 (P0), RWIN3.P$2 (P0)
unnamed: D11.A, LWIN.MX1 (P0), LWIN.P$1 (P0), LWIN.P$2 (P0), LWIN1.MX2 (P1), LWIN1.P$3 (P1), LWIN1.P$4 (P1)
unnamed: D10.A, LALT.MX1 (P0), LALT.P$1 (P0), LALT.P$2 (P0), LALT1.MX2 (P1), LALT1.P$3 (P1), LALT1.P$4 (P1)
unnamed: D13.A, FN.MX2 (P1), FN.P$3 (P1), FN.P$4 (P1)
unnamed: D65.A, ~1.MX2 (P1), ~1.P$3 (P1), ~1.P$4 (P1)
unnamed: D66.A, TAB1.MX2 (P1), TAB1.P$3 (P1), TAB1.P$4 (P1)
unnamed: D67.A, TAB2.MX2 (P1), TAB2.P$3 (P1), TAB2.P$4 (P1)
unnamed: BCKSPC.MX1 (P0), BCKSPC.P$1 (P0), BCKSPC.P$2 (P0), D33.A, \\.MX2 (P1), \\.P$3 (P1), \\.P$4 (P1)
unnamed: D68.A, TAB3.MX2 (P1), TAB3.P$3 (P1), TAB3.P$4 (P1)
unnamed: D69.A, TAB4.MX2 (P1), TAB4.P$3 (P1), TAB4.P$4 (P1)
unnamed: =1.MX2 (P1), =1.P$3 (P1), =1.P$4 (P1), D70.A
unnamed: D6.A, RALT1.MX2 (P1), RALT1.P$3 (P1), RALT1.P$4 (P1)
unnamed: =2.MX2 (P1), =2.P$3 (P1), =2.P$4 (P1), D71.A
unnamed: 1.MX1 (P0), 1.P$1 (P0), 1.P$2 (P0), D22.A
unnamed: 2.MX2 (P1), 2.P$3 (P1), 2.P$4 (P1), D23.A
unnamed: 3.MX2 (P1), 3.P$3 (P1), 3.P$4 (P1), D24.A
unnamed: 4.MX2 (P1), 4.P$3 (P1), 4.P$4 (P1), D25.A
unnamed: 5.MX2 (P1), 5.P$3 (P1), 5.P$4 (P1), D26.A
unnamed: 6.MX2 (P1), 6.P$3 (P1), 6.P$4 (P1), D27.A
unnamed: 7.MX2 (P1), 7.P$3 (P1), 7.P$4 (P1), D28.A
unnamed: 8.MX2 (P1), 8.P$3 (P1), 8.P$4 (P1), D29.A
unnamed: 0.MX2 (P1), 0.P$3 (P1), 0.P$4 (P1), D30.A
unnamed: -.MX2 (P1), -.P$3 (P1), -.P$4 (P1), D31.A
unnamed: =.MX2 (P1), =.P$3 (P1), =.P$4 (P1), D32.A
unnamed: =3.MX2 (P1), =3.P$3 (P1), =3.P$4 (P1), D72.A
unnamed: D34.A, DEL.MX2 (P1), DEL.P$3 (P1), DEL.P$4 (P1)
unnamed: =4.MX2 (P1), =4.P$3 (P1), =4.P$4 (P1), D73.A
unnamed: 9.MX2 (P1), 9.P$3 (P1), 9.P$4 (P1), D36.A
unnamed: D37.A, Q.MX2 (P1), Q.P$3 (P1), Q.P$4 (P1)
unnamed: D38.A, W.MX2 (P1), W.P$3 (P1), W.P$4 (P1)
unnamed: D39.A, E.MX2 (P1), E.P$3 (P1), E.P$4 (P1)
unnamed: D40.A, R.MX2 (P1), R.P$3 (P1), R.P$4 (P1)
unnamed: D41.A, T.MX2 (P1), T.P$3 (P1), T.P$4 (P1)
unnamed: D42.A, Y.MX2 (P1), Y.P$3 (P1), Y.P$4 (P1)
unnamed: D43.A, U.MX2 (P1), U.P$3 (P1), U.P$4 (P1)
unnamed: D9.A, RCTRL.MX2 (P1), RCTRL.P$3 (P1), RCTRL.P$4 (P1), RCTRL1.MX1 (P0), RCTRL1.P$1 (P0), RCTRL1.P$2 (P0)
unnamed: =5.MX2 (P1), =5.P$3 (P1), =5.P$4 (P1), D74.A
unnamed: Q5.1 (G), R11.2, R12.1
unnamed: Q4.1 (G), Q5.3 (D), R10.1
unnamed: D44.A, I.MX2 (P1), I.P$3 (P1), I.P$4 (P1)
unnamed: D51.A, O.MX2 (P1), O.P$3 (P1), O.P$4 (P1)
unnamed: D45.A, P.MX2 (P1), P.P$3 (P1), P.P$4 (P1)
unnamed: D46.A, [.MX2 (P1), [.P$3 (P1), [.P$4 (P1)
unnamed: D47.A, ].MX2 (P1), ].P$3 (P1), ].P$4 (P1)
unnamed: D4.A, LSHIFT.MX1 (P0), LSHIFT.P$1 (P0), LSHIFT.P$2 (P0), LSHIFT1.MX2 (P1), LSHIFT1.P$3 (P1), LSHIFT1.P$4 (P1)
unnamed: D48.A, |.MX2 (P1), |.P$3 (P1), |.P$4 (P1)
unnamed: A.MX2 (P1), A.P$3 (P1), A.P$4 (P1), D49.A
unnamed: D52.A, S.MX2 (P1), S.P$3 (P1), S.P$4 (P1)
unnamed: D.MX2 (P1), D.P$3 (P1), D.P$4 (P1), D53.A
unnamed: D54.A, F.MX2 (P1), F.P$3 (P1), F.P$4 (P1)
unnamed: D55.A, G.MX2 (P1), G.P$3 (P1), G.P$4 (P1)
unnamed: D56.A, H.MX2 (P1), H.P$3 (P1), H.P$4 (P1)
unnamed: D57.A, J.MX2 (P1), J.P$3 (P1), J.P$4 (P1)
unnamed: D58.A, K.MX2 (P1), K.P$3 (P1), K.P$4 (P1)
unnamed: D50.A, L.MX2 (P1), L.P$3 (P1), L.P$4 (P1)
unnamed: ...MX2 (P1), ...P$3 (P1), ...P$4 (P1), D59.A
unnamed: '.MX2 (P1), '.P$3 (P1), '.P$4 (P1), D60.A
unnamed: D61.A, ENTER.MX2 (P1), ENTER.P$3 (P1), ENTER.P$4 (P1)
unnamed: RGB17.1 (DO), RGB18.3 (DI)
unnamed: RGB16.1 (DO), RGB17.3 (DI)
unnamed: BAT.1 (2), S3.3 (S), X6.2
unnamed: J1.A5 (CC1), R1.2
unnamed: J1.B5 (CC2), R2.2
unnamed: Q1.5 (PROG), R6.2
unnamed: D63.A, Z.MX2 (P1), Z.P$3 (P1), Z.P$4 (P1)
unnamed: D35.A, X.MX2 (P1), X.P$3 (P1), X.P$4 (P1)
unnamed: C.MX2 (P1), C.P$3 (P1), C.P$4 (P1), D21.A
unnamed: D20.A, V.MX2 (P1), V.P$3 (P1), V.P$4 (P1)
unnamed: B.MX2 (P1), B.P$3 (P1), B.P$4 (P1), D19.A
unnamed: D18.A, N.MX2 (P1), N.P$3 (P1), N.P$4 (P1)
unnamed: D17.A, M.MX2 (P1), M.P$3 (P1), M.P$4 (P1)
unnamed: ,.MX2 (P1), ,.P$3 (P1), ,.P$4 (P1), D12.A
unnamed: ..MX2 (P1), ..P$3 (P1), ..P$4 (P1), D16.A
unnamed: /.MX2 (P1), /.P$3 (P1), /.P$4 (P1), D15.A
unnamed: RGB1.1 (DO), RGB2.3 (DI)
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
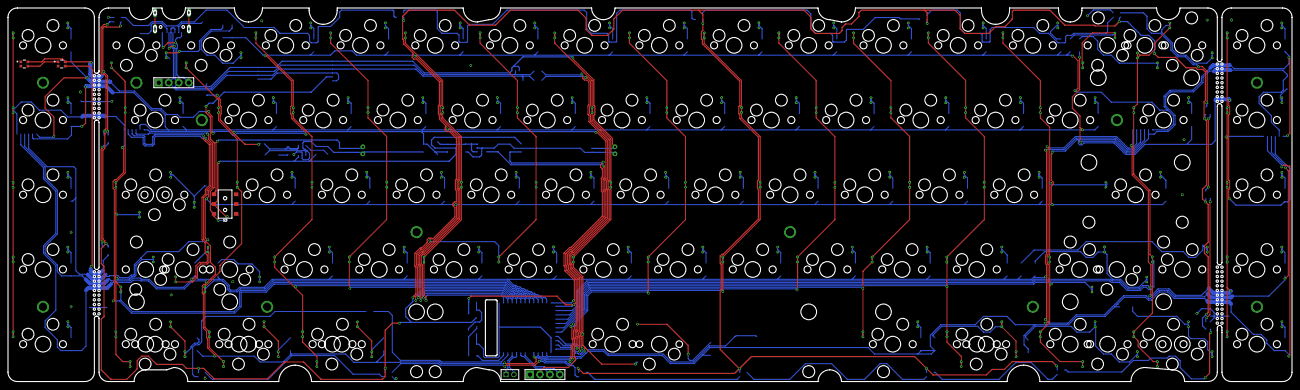
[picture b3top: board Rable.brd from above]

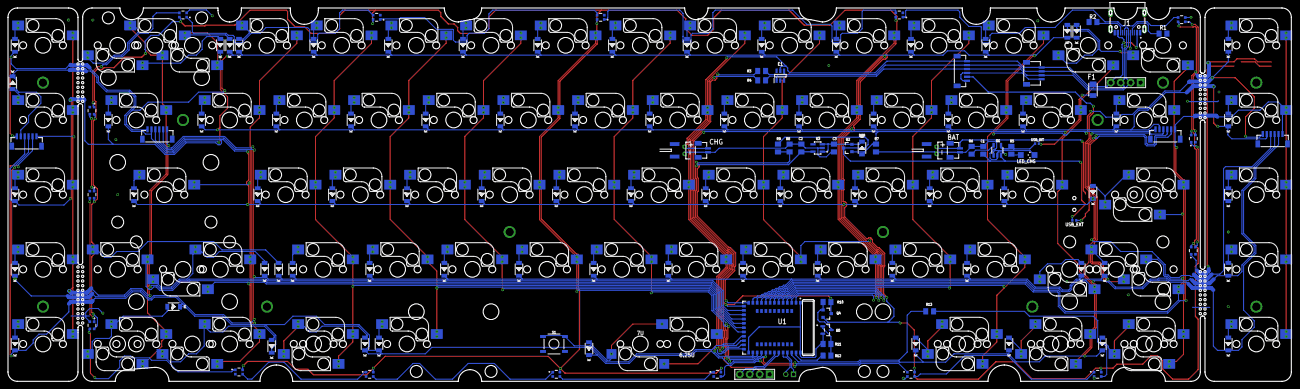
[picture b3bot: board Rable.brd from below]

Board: 2 copper layers, 327.4 x 95.2 mm, 221 parts (215 on the bottom side), 142 nets.
